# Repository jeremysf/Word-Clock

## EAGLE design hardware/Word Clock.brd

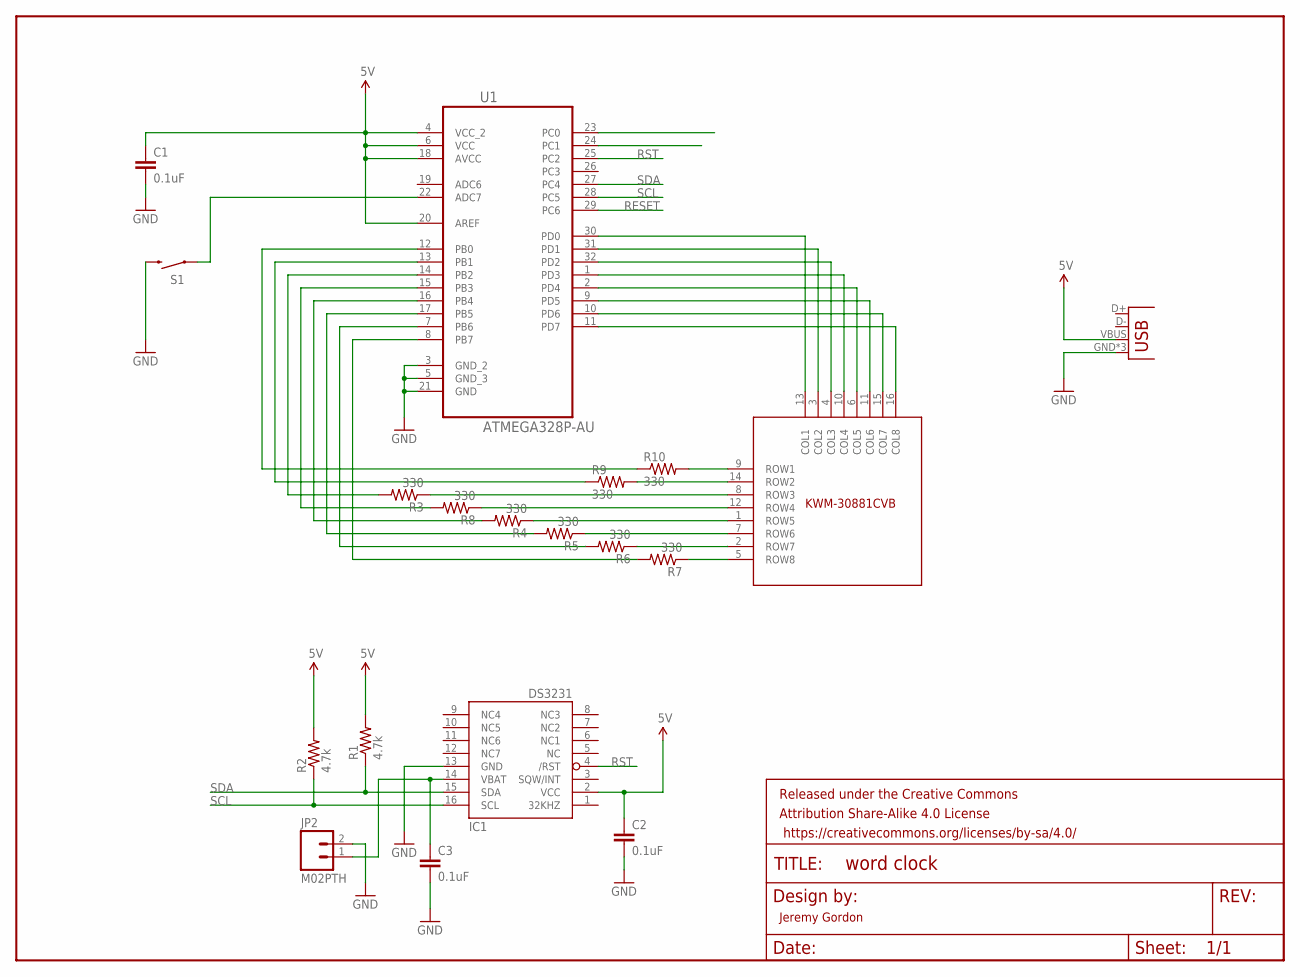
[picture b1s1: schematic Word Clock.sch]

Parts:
C1, C2, C3: 0.1uF; 0805
D1: KWM-30881CVB
FRAME1: FRAME-LETTER; CREATIVE_COMMONS
IC1: DS3231/SO; SO16W
JP1: USB-MICROB
JP2: M02PTH; 1X02
R1, R2: 4.7k; 0805
R3, R4, R5, R6, R7, R8, R9, R10: 330; 0805
S1: SWITCH-MOMENTARY-2SMD-1101NE; TACTILE-SWITCH-1101NE
U1: ATMEGA328P-AU; QFP80P900X900X120-32N

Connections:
5V: C1.1, C2.1, IC1.2 (VCC), JP1.VBUS, R1.2, R2.2, U1.4 (VCC_2), U1.6 (VCC), U1.18 (AVCC), U1.20 (AREF)
GND: C1.2, C2.2, C3.2, IC1.13 (GND), JP1.GND, JP1.MT1 (GND), JP1.MT2 (GND), JP2.2, S1.2, U1.3 (GND_2), U1.5 (GND_3), U1.21 (GND)
unnamed: D1.13 (COL1), U1.30 (PD0)
unnamed: D1.3 (COL2), U1.31 (PD1)
unnamed: D1.4 (COL3), U1.32 (PD2)
unnamed: D1.10 (COL4), U1.1 (PD3)
unnamed: D1.6 (COL5), U1.2 (PD4)
unnamed: D1.11 (COL6), U1.9 (PD5)
unnamed: D1.15 (COL7), U1.10 (PD6)
unnamed: D1.16 (COL8), U1.11 (PD7)
unnamed: R9.1, U1.13 (PB1)
unnamed: R8.2, U1.15 (PB3)
unnamed: R4.2, U1.16 (PB4)
unnamed: R5.2, U1.17 (PB5)
unnamed: R10.1, U1.12 (PB0)
unnamed: C3.1, IC1.14 (VBAT), JP2.1
unnamed: S1.1, U1.22 (ADC7)
unnamed: D1.8 (ROW3), R3.1
unnamed: D1.12 (ROW4), R8.1
unnamed: D1.1 (ROW5), R4.1
unnamed: D1.7 (ROW6), R5.1
unnamed: D1.2 (ROW7), R6.1
unnamed: D1.5 (ROW8), R7.1
unnamed: D1.9 (ROW1), R10.2
unnamed: D1.14 (ROW2), R9.2
unnamed: R6.2, U1.7 (PB6)
unnamed: R7.2, U1.8 (PB7)
unnamed: R3.2, U1.14 (PB2)
RESET: U1.29 (PC6)
RST: IC1.4 (/RST), U1.25 (PC2)
SCL: IC1.16 (SCL), R2.1, U1.28 (PC5)
SDA: IC1.15 (SDA), R1.1, U1.27 (PC4)

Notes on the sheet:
Jeremy Gordon

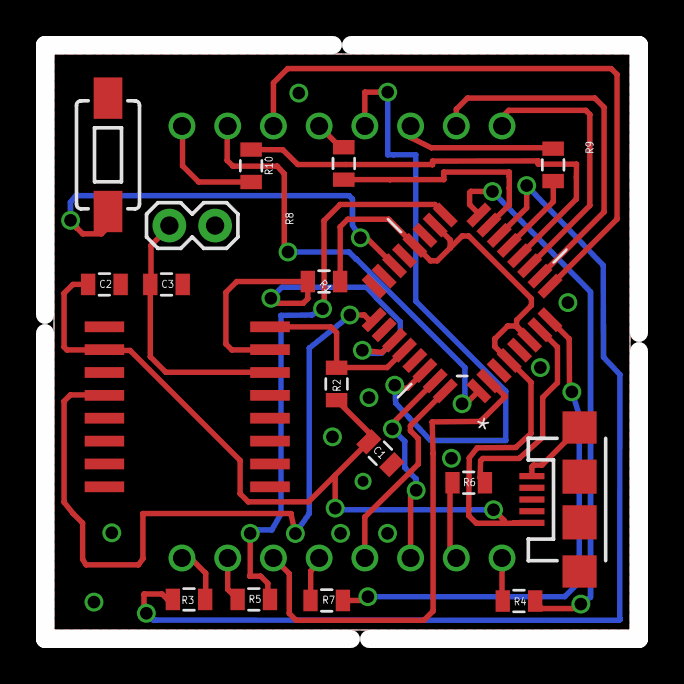
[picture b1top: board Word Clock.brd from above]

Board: 2 copper layers, 32.0 x 32.0 mm, 20 parts (1 on the bottom side), 31 nets.

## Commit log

2014-12-09 Initial commit.
2014-12-09 Removed MAX7219, driving with raw atmega.
2014-12-15 Upped isloate and generally tweaked board to be more Cirqoid friendly.
2014-12-16 Cleaner .gitignore.
2014-12-21 More updates to .gitignore.
2014-12-26 Fixing errant use of ADC lines and revised for 0.6mm vias.
2015-01-12 0.7mm for rivets.

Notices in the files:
parts and their libraries:
SparkFun-Aesthetics: Licensing: Creative Commons ShareAlike 4.0 International - https://creativecommons.org/licenses/by-sa/4.0
SparkFun-Aesthetics: Released under the Creative Commons Attribution Share-Alike 4.0 License
SparkFun-Aesthetics: https://creativecommons.org/licenses/by-sa/4.0
